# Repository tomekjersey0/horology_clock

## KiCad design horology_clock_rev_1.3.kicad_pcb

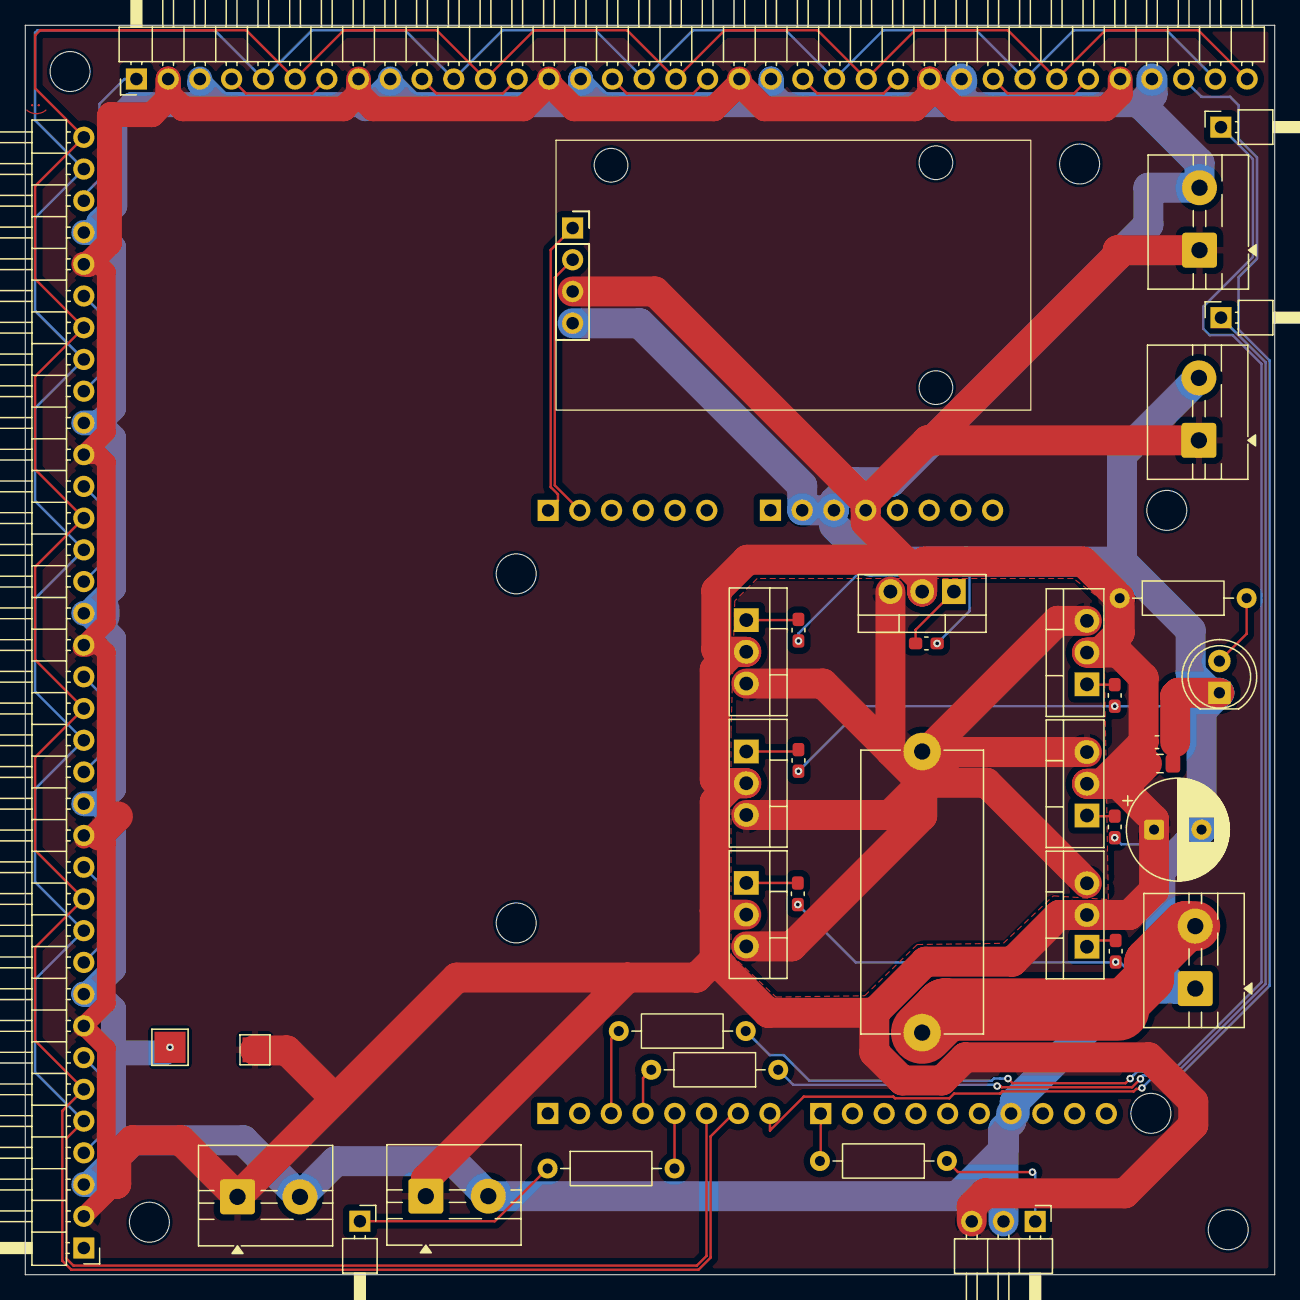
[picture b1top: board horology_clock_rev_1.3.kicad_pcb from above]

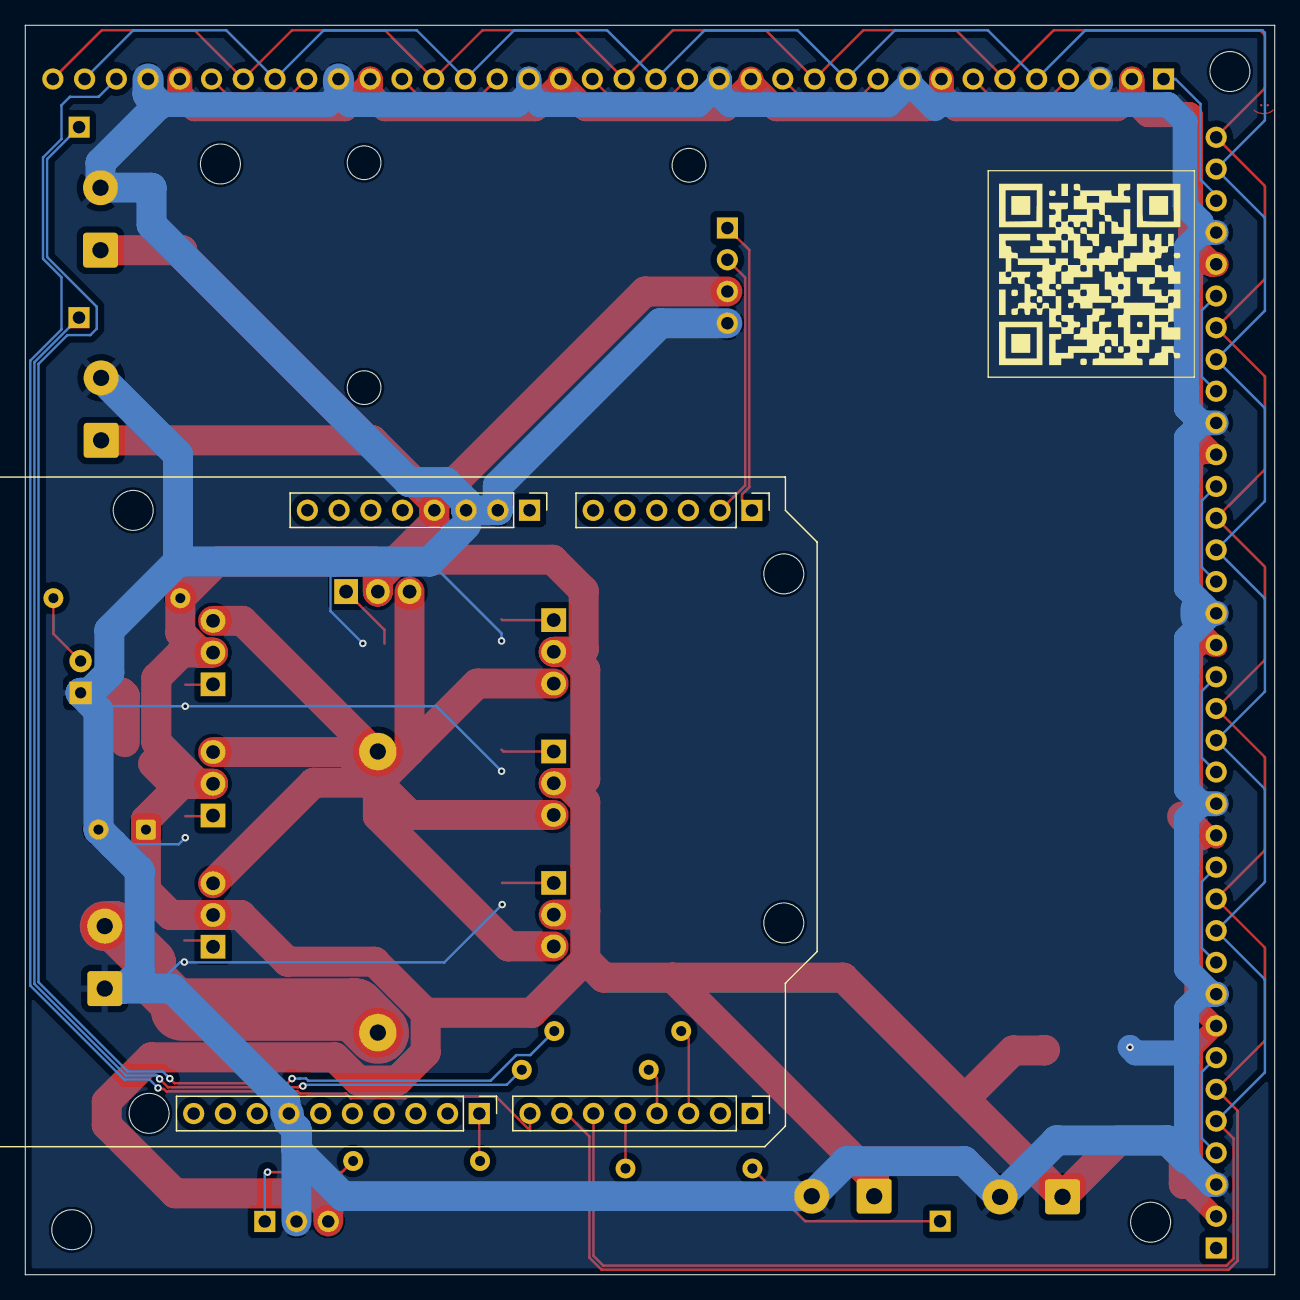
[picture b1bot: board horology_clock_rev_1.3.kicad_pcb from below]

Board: 2 copper layers, 100.0 x 100.0 mm, 48 parts (5 on the bottom side), 36 nets.

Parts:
A1: Arduino_UNO_R3; Arduino_UNO_R3_WithMountingHoles_Standoff_Mounted
C1: 1000uF; CP_Radial_D8.0mm_P3.80mm
C2: 10uF; C_0805_2012Metric_Pad1.18x1.45mm_HandSolder
C3: 100nF; C_0603_1608Metric_Pad1.08x0.95mm_HandSolder
D1: LED; LED_D5.0mm
F1: Fuse; Fuseholder_Cylinder-5x20mm_Schurter_0031_8201_Horizontal_Op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
H1, H2, H3, H4: MountingHole; MountingHole_3.2mm_M3
J1, J2: Conn_01x36; PinHeader_1x36_P2.54mm_Horizontal
J3, J4, J5, J7, J11: Screw_Terminal_01x02; TerminalBlock_MaiXu_MX126-5.0-02P_1x02_P5.00mm
J6: Conn_01x06; PinHeader_1x06_P2.54mm_Vertical
J8, J10: Conn_01x08; PinHeader_1x08_P2.54mm_Vertical
J9: Conn_01x03; PinHeader_1x03_P2.54mm_Horizontal
J13: Conn_01x04; PinSocket_1x04_P2.54mm_Vertical
J14: Conn_01x10; PinHeader_1x10_P2.54mm_Vertical
J15, J16, J17: Conn_01x01; PinHeader_1x01_P2.54mm_Horizontal
Q1, Q2, Q3, Q4, Q5, Q6, Q7: IRF9540N; TO-220-3_Vertical
R1, R2, R3, R4: 330Ω; R_Axial_DIN0207_L6.3mm_D2.5mm_P10.16mm_Horizontal
R5, R6, R7, R8, R9, R10, R11: 100kΩ; C_0603_1608Metric_Pad1.08x0.95mm_HandSolder
R12: 1kΩ; R_Axial_DIN0207_L6.3mm_D2.5mm_P10.16mm_Horizontal
TP1: TestPoint; TestPoint_Pad_2.5x2.5mm
TP2: TestPoint; TestPoint_Pad_2.0x2.0mm
U1: DS3231

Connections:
7SEG_DATA: J16.1, R3.1
+5V: C1.1, C2.1, C3.1, J1.2, J1.8, J1.14, J1.20, J1.26, J1.32, J2.2, J2.8, J2.14, J2.20, J2.26, J2.32, J3.1, J4.1, J5.1, J8.4, J9.3, J11.1, J13.3, Q1.2 (D), Q2.2 (D), Q3.2 (D), Q4.2 (D), Q5.2 (D), Q6.2 (D), Q7.2 (D), R12.2, TP2.1
BINARY_DATA: J17.1, R2.1
DOTS_DATA: J15.1, R4.1
GND: C1.2, C2.2, C3.2, D1.1 (K), J1.3, J1.9, J1.15, J1.21, J1.27, J1.33, J2.3, J2.9, J2.15, J2.21, J2.27, J2.33, J3.2, J4.2, J5.2, J7.1, J8.2, J8.3, J9.2, J11.2, J13.4, J14.7 (RESET), R5.2, R6.2, R7.2, R8.2, R9.2, R10.2, R11.2, TP1.1
HEART_BEAT_DATA: J9.1, R1.1
MAX_CLK: J1.6, J1.12, J1.18, J1.24, J1.30, J1.36, J2.6, J2.12, J2.18, J2.24, J2.30, J2.36, J10.7
MAX_CS: J1.5, J1.11, J1.17, J1.23, J1.29, J1.35, J2.5, J2.11, J2.17, J2.23, J2.29, J2.35, J10.6
MAX_DIN: J1.34, J10.8
unnamed: D1.2 (A), R12.1
unnamed: J1.1, J2.34
unnamed: J1.4, J1.7
unnamed: J1.10, J1.13
unnamed: J1.16, J1.19
unnamed: J1.22, J1.25
unnamed: J1.28, J1.31
unnamed: J2.4, J2.7
unnamed: J2.10, J2.13
unnamed: J2.16, J2.19
unnamed: J2.22, J2.25
unnamed: J2.28, J2.31
unnamed: J10.3, R2.2
unnamed: J10.4, R3.2
unnamed: J10.5, R4.2
unnamed: J14.1 (3.3V), R1.2
unnamed: Q1.1 (G), R5.1
unnamed: Q2.1 (G), R6.1
unnamed: Q3.1 (G), R7.1
unnamed: Q4.1 (G), R8.1
unnamed: Q5.1 (G), R9.1
unnamed: Q6.1 (G), R10.1
unnamed: Q7.1 (G), R11.1
RTC_SCL: J6.1, J13.1
RTC_SDA: J6.2, J13.2
VIN_PROTECTED: F1.2, Q1.3 (S), Q2.3 (S), Q3.3 (S), Q4.3 (S), Q5.3 (S), Q6.3 (S), Q7.3 (S)
VIN_RAW: F1.1, J7.2

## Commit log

2026-03-03 Initial commit - horology clock rev1.3 baseline
2026-03-03 completed main power distribution redesign - power connector on top right edge
2026-03-04 Added Arduino on underside. Arduino USB below main power plug.
2026-03-05 Corrected Power Order: Now POWER -> FUSE -> MOSFETS
2026-03-05 Added silkscreen component identifiers.
2026-03-05 Adjusted some traces.
2026-03-06 Moved Arduino such that mounting holes for all components dont intersect other each others footprints.
2026-03-06 Minor changes.
2026-03-07 Moved Pin 1 to Pin 8 to avoid Serial Issues.
2026-03-08 Grouped Data and Power ouputs into close physical units.
2026-03-12 Spaced the MOSFETs out around the Fuse for easy access with fat fingies.
2026-03-12 Moved the terminals to their final locations, and connected everything together.
2026-03-13 Ready for Fab.
2026-03-13 Removed all F.Silk text.
2026-03-13 Removed all B.silk text.
2026-03-13 Added folders for export
2026-03-13 Cleaned up working directory
2026-03-13 Removed redundant old lib
2026-03-13 Deleted redundant files
